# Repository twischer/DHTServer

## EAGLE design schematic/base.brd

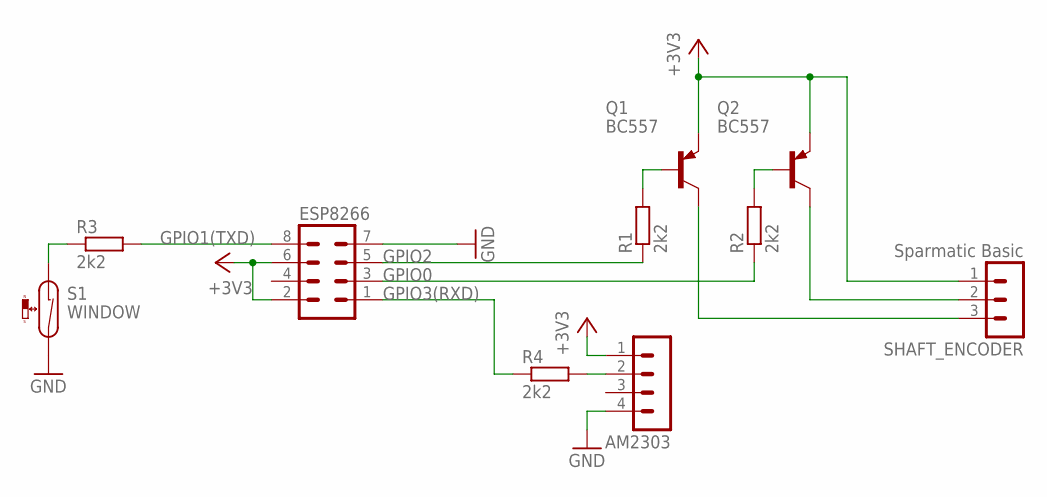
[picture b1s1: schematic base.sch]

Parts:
AM2303: MA04-1
ESP8266: MA04-2
Q1, Q2: BC557; TO92-EBC
R1, R2, R3, R4: 2k2; 0204/7
S1: WINDOW; MK6-8-A
SHAFT_ENCODER: Sparmatic Basic; MA03-1

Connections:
+3V3: AM2303.1, ESP8266.2, ESP8266.6, Q1.E, Q2.E, SHAFT_ENCODER.1
GND: AM2303.4, ESP8266.7, S1.2
GPIO0: ESP8266.3, R2.1
GPIO1(TXD): ESP8266.8, R3.2
GPIO2: ESP8266.5, R1.1
GPIO3(RXD): ESP8266.1, R4.1
unnamed: Q1.B, R1.2
unnamed: Q2.B, R2.2
unnamed: R3.1, S1.1
unnamed: Q2.C, SHAFT_ENCODER.2
unnamed: Q1.C, SHAFT_ENCODER.3
unnamed: AM2303.2, R4.2

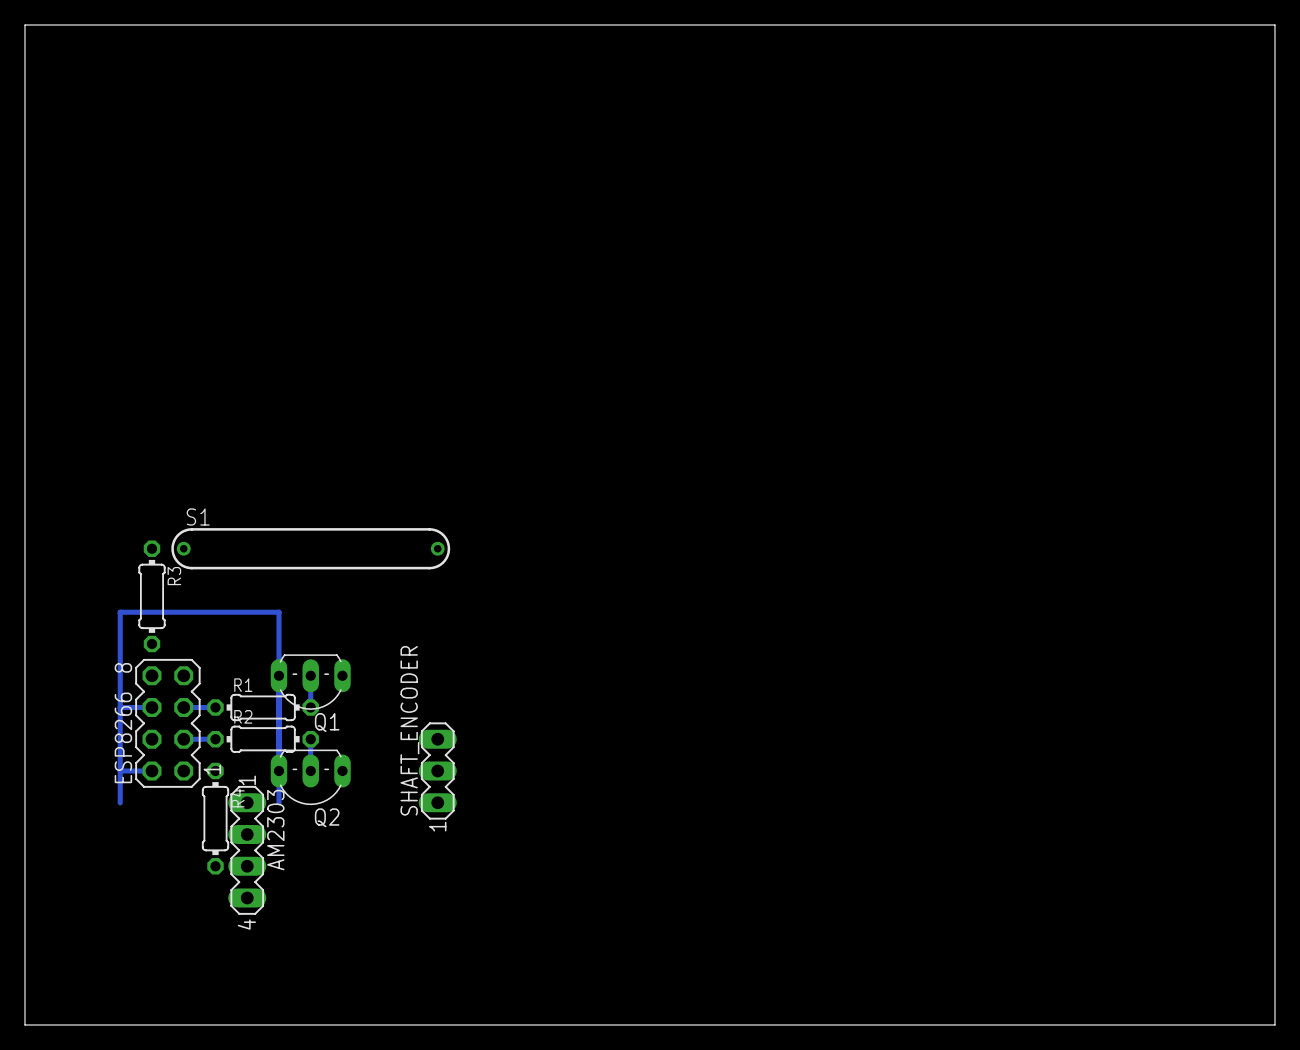
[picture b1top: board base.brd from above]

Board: 2 copper layers, 100.0 x 80.0 mm, 10 parts (0 on the bottom side), 12 nets.

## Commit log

2015-10-04 Add inital sparmatric basic controller
2015-10-04 Add schematic
2015-10-04 Rename Arduino project file because of unsing a different directory
2015-10-04 Slow done shaft encoder simulation for long wires
2015-10-04 Add script for temperature logging
2015-10-29 Use response time as time stamp for the new data line in the logger script
2015-11-20 Set termopstat temparatur one degree higher
2015-11-20 Add tools for heater control
2015-11-20 Add DHT to sematic
2015-11-20 Restoring last temperature form flash after restart
2015-11-20 Revert "Set termopstat temparatur one degree higher"
    This reverts commit afbf21ab4505d5594038a130ca3e03a73ab483a1.
